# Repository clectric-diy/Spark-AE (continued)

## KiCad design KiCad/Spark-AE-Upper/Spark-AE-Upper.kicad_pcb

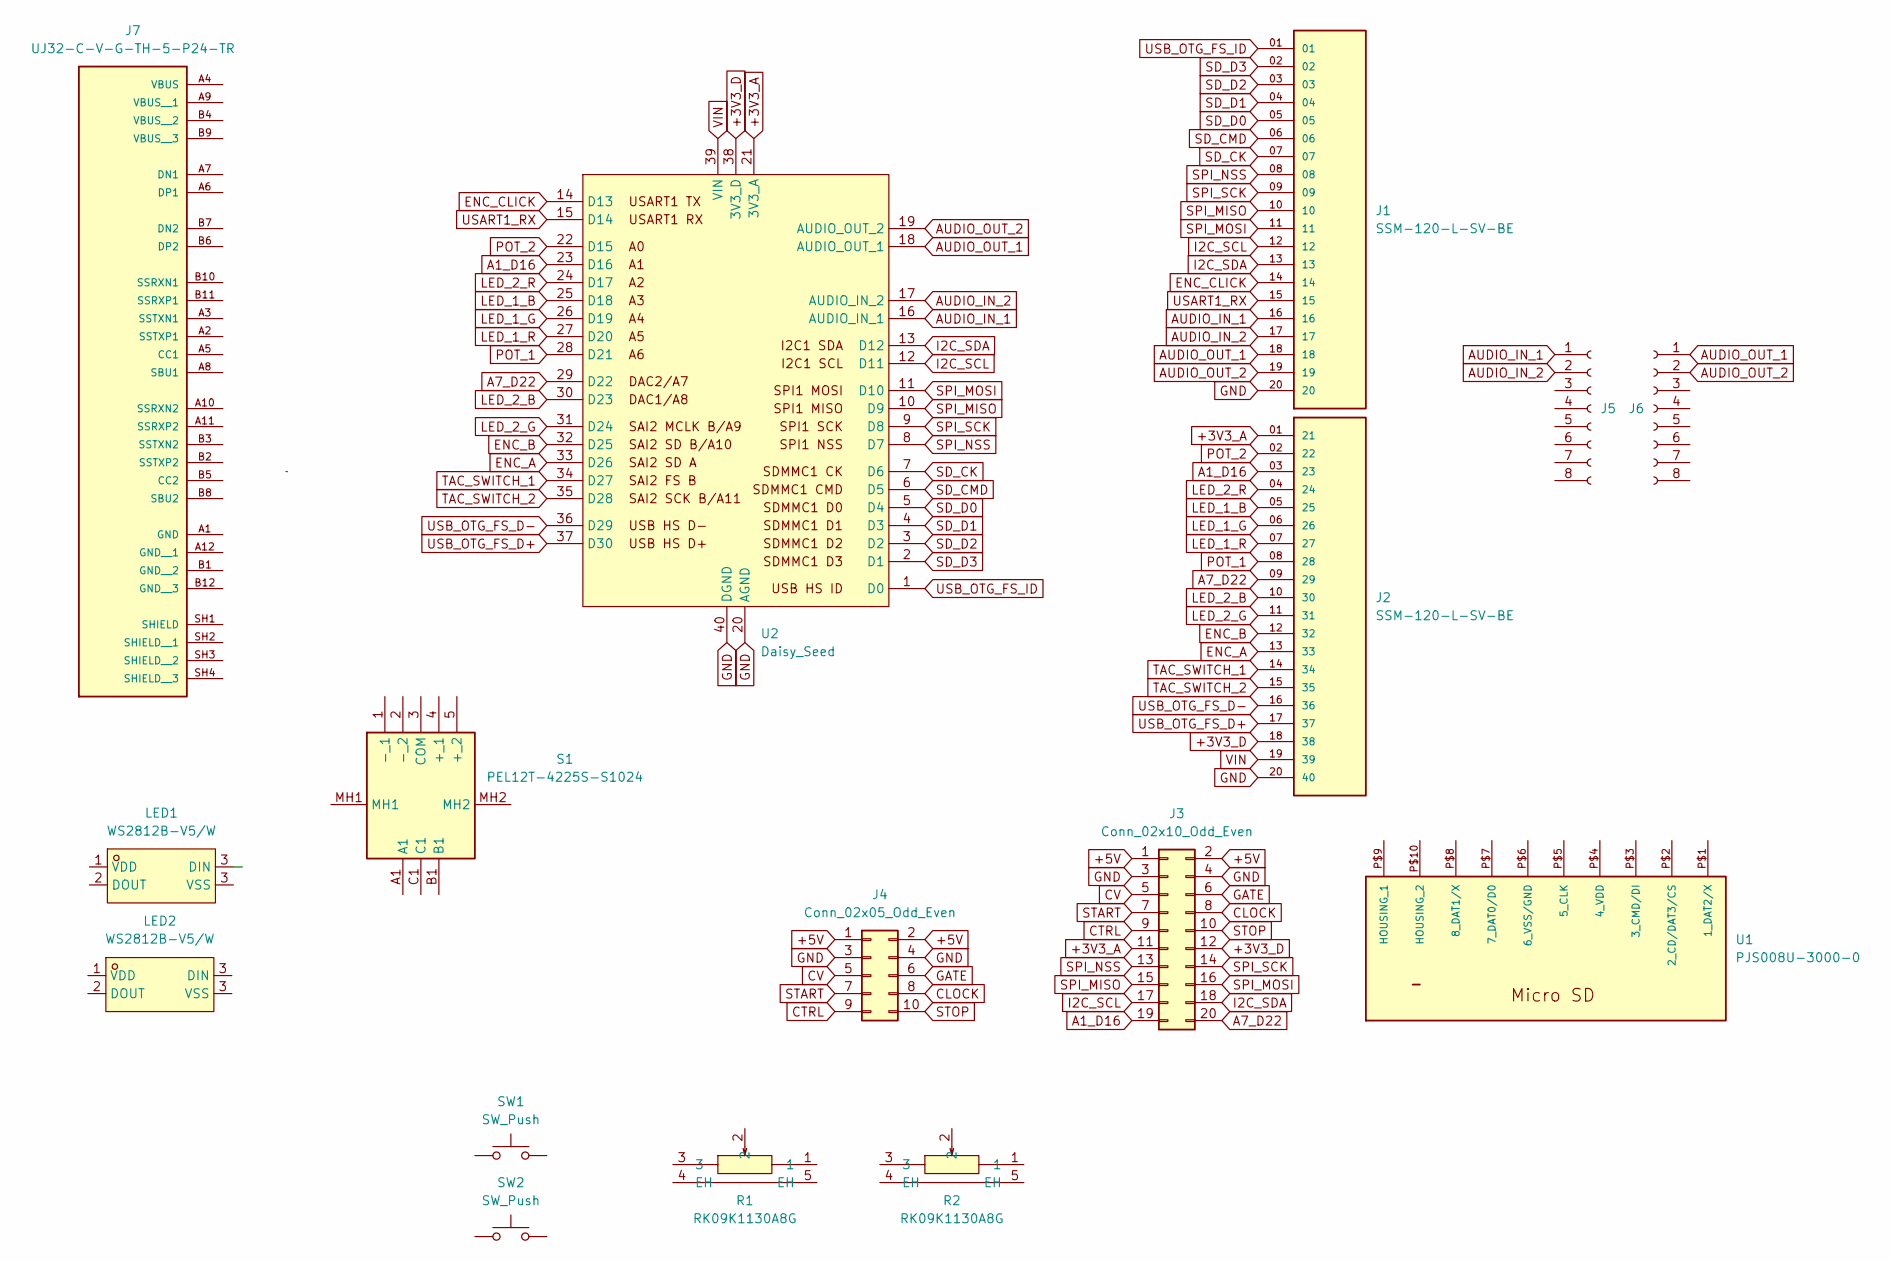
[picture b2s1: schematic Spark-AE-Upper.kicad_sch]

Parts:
J1, J2: SSM-120-L-SV-BE; SAMTEC_SSM-120-L-SV-BE
J3: Conn_02x10_Odd_Even; PinHeader_2x10_P2.54mm_Vertical
J4: Conn_02x05_Odd_Even; PinHeader_2x05_P2.54mm_Vertical
J5, J6: Conn_01x08_Socket; PinSocket_1x08_P2.54mm_Vertical
J7: UJ32-C-V-G-TH-5-P24-TR; SAMESKY_UJ32-C-V-G-TH-5-P24-TR; PARTREV 1.0
LED1, LED2: WS2812B-V5/W; LED-SMD_4P-L5.0-W5.0-TL-1; LCSC Part C2874885
R1, R2: RK09K1130A8G; RES-TH_RK09K113004U; LCSC Part C470294
S1: PEL12T-4225S-S1024; PEL12T4225SS1024; Mouser Part Number 652-PEL12T4225SS1024
SW1, SW2: SW_Push; SW_PUSH_6mm
U1: PJS008U-3000-0
U2: Daisy_Seed; DAISY_SEED

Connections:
+3V3_A: J2.01 (21), J3.11, U2.21 (3V3_A)
+3V3_D: J2.18 (38), J3.12, U2.38 (3V3_D)
+5V: J3.1, J3.2, J4.1, J4.2
A1_D16: J2.03 (23), J3.19, U2.23 (D16)
A7_D22: J2.09 (29), J3.20, U2.29 (D22)
AUDIO_IN_1: J1.16, J5.1, U2.16 (AUDIO_IN_1)
AUDIO_IN_2: J1.17, J5.2, U2.17 (AUDIO_IN_2)
AUDIO_OUT_1: J1.18, J6.1, U2.18 (AUDIO_OUT_1)
AUDIO_OUT_2: J1.19, J6.2, U2.19 (AUDIO_OUT_2)
CLOCK: J3.8, J4.8
CTRL: J3.9, J4.9
CV: J3.5, J4.5
ENC_A: J2.13 (33), U2.33 (D26)
ENC_B: J2.12 (32), U2.32 (D25)
ENC_CLICK: J1.14, U2.14 (D13)
GATE: J3.6, J4.6
GND: J1.20, J2.20 (40), J3.3, J3.4, J4.3, J4.4, U2.20 (AGND), U2.40 (DGND)
I2C_SCL: J1.12, J3.17, U2.12 (D11)
I2C_SDA: J1.13, J3.18, U2.13 (D12)
LED_1_B: J2.05 (25), U2.25 (D18)
LED_1_G: J2.06 (26), U2.26 (D19)
LED_1_R: J2.07 (27), U2.27 (D20)
LED_2_B: J2.10 (30), U2.30 (D23)
LED_2_G: J2.11 (31), U2.31 (D24)
LED_2_R: J2.04 (24), U2.24 (D17)
POT_1: J2.08 (28), U2.28 (D21)
POT_2: J2.02 (22), U2.22 (D15)
SD_CK: J1.07, U2.7 (D6)
SD_CMD: J1.06, U2.6 (D5)
SD_D0: J1.05, U2.5 (D4)
SD_D1: J1.04, U2.4 (D3)
SD_D2: J1.03, U2.3 (D2)
SD_D3: J1.02, U2.2 (D1)
SPI_MISO: J1.10, J3.15, U2.10 (D9)
SPI_MOSI: J1.11, J3.16, U2.11 (D10)
SPI_NSS: J1.08, J3.13, U2.8 (D7)
SPI_SCK: J1.09, J3.14, U2.9 (D8)
START: J3.7, J4.7
STOP: J3.10, J4.10
TAC_SWITCH_1: J2.14 (34), U2.34 (D27)
TAC_SWITCH_2: J2.15 (35), U2.35 (D28)
USART1_RX: J1.15, U2.15 (D14)
USB_OTG_FS_D+: J2.17 (37), U2.37 (D30)
USB_OTG_FS_D-: J2.16 (36), U2.36 (D29)
USB_OTG_FS_ID: J1.01, U2.1 (D0)
VIN: J2.19 (39), U2.39 (VIN)

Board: 2 copper layers, 16 parts (3 on the bottom side), 46 nets, no tracks yet.

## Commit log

2025-07-31 Create LICENSE
2025-08-03 Rebranding
    I'm rebranding everything to respect Electrosmith's trademarks. I got carried away. The new names align with the company name and make more sense anyway.
2025-08-08 Explaining the CERN OHL implications.
2025-08-09 I bumped my head and the ~~flux capacitor~~ Arc was revealed.
2025-08-09 Adding stubs for Arc modules.
2025-08-09 Removing the clectric Branding from the Arc modules.
2025-08-09 Initial commit of KiCad files
2025-08-09 Ignoring KiCad cache and backups
2025-08-09 Added Daisy Seed
2025-08-10 Create CONTRIBUTING.md file with contribution guidelines.
2025-08-10 Update README.md
    Added reference and link to the Daisy Seed in the Features section.
2025-08-15 Updating Contrib
2025-08-16 Adding docs directory.
2025-08-18 Moving _config.yml
2025-08-18 Oops, wrong theme.
2025-08-19 Added Electrosmith Source Docs
2025-08-22 Adding 1st Sketches of Spark-AE
2025-08-22 Added 1st Sketch and Updated Design Goals
2025-08-22 bump for pages
2025-08-22 Remove Download visit GitHub
2025-08-22 Font looked weird.
2025-08-22 panels not faceplates
2025-08-22 Moving KiCad files into subdirectory
2025-08-24 Cleaning up extra file in repo and README headings
2025-08-24 Apparently Markdown Syntax not supported.
2025-08-24 Standard FUNDING & gitignore
2025-09-01 Adding pdf version of module dimensions for Quickswap Case
2025-09-01 Committed to wrong repo.
2025-09-02 Reducing Headers and Updating Protoboards link.
2025-09-03 Ignoring Gerbers. Trust but verify.
2025-10-12 Found an Rotary Encoder that I think will match the AE style.
2025-10-13 Removing because part is not tested and confirmed yet.
2025-10-13 Roughing out the basic edges and control layout.
2026-01-14 removed led holes in favor of transparent pots
2026-01-14 renamed initial to panel and added other pcb projects
2026-01-14 filled in title blocks
2026-01-15 bumping copyright year
2026-01-15 updated to use components from clectric-diy's library
2026-01-22 laid out upper board interface and connections
2026-01-22 added first render of the pcb
2026-01-23 added and connected nets for daisy seed socket
2026-01-23 updated footprints and models
2026-01-23 added nets for bus connectors
2026-01-23 repositioned daisy seed, usb c, and micro sd
2026-01-23 ignoring working files
2026-01-23 added nets for ae modular i/o headers
2026-01-24 renamed nets to match pod and added arc connector
2026-01-24 positioned arc connector and repositioned daisy seed
2026-01-24 repositioned switches
2026-02-01 removing lower pcb and renaming to reflect change
2026-02-01 reorganizing the location of the Arc files
2026-02-03 renamed board to reduce board count
2026-03-09 moving over progress from "Shock" (see desc)
    I attempted to create this Daisy Pod clone as an AE-1U module called the "Shock". As expected I couldn't make it work.
    I've moved my progress on the "Shock" schematic over to and replacing the work on the "Spark".
    I plan to go back to make the "Shock" a stripped down version of the "Spark" in an AE-1U format.
2026-03-10 initial committ of completely reworked schematic. thanks gemini!
2026-03-12 assigned footprints & sorted ratsnest
2026-03-21 adding kicad_dru file with constraints for JLCPCB manufacturing and assembly
2026-03-21 ignoring KiCad backup files
2026-03-21 schematic 100% complete. pcb layout around 50% complete.
2026-03-22 continuing to plug away at pcb layout
2026-03-23 I accdently upgraded to KiCad 10 via a `brew upgrade`. I committing before launching it just in case.
2026-03-27 pcb layout complete. ready for final pre-fab confirmation.
2026-03-27 ignoring kicad fabrication files.
2026-03-27 Revise README for Mk0 Prototype details and edits
    Updated README to reflect changes in the Mk0 Prototype and removed a line about vertical symmetry.
2026-03-27 mk0 prototype sent for production! commit includes a couple of necessary tweaks.
2026-03-27 mk0 render for project readme
2026-03-27 ignoring fabrication files
2026-04-11 Restructuring directories to separate Arcs and to allow for duplicate panels
2026-04-16 bumped version to Mk0.1 and corrected polarity of D4 on schematic
2026-04-26 renaming images to show mark progression
2026-04-26 adding Mk0.1 schematic
2026-04-26 testing serving GitHub Pages from docs
2026-04-26 renaming images for more accurate versioning
2026-04-26 renamed Mk0.0 prototype images
    Updated the image reference for the Mk0 Prototype render.
2026-04-26 updated to Mk0.0 for more accurate prototype versioning
2026-04-26 committing to GitHub Pages served from docs
2026-04-26 actually pulling GitHub Pages content over this time
2026-04-26 correctiing typo
2026-04-26 Fix image path for Mk0 Prototype in README
    Updated image path for Mk0 Prototype render in README.
2026-04-26 bumping version number
2026-04-26 reorganizing to allow for alternate panels
2026-04-26 moving arcs back under spark instead
2026-04-26 rough pass over original mk0.1 panel. needs confirmation.
2026-04-26 made lightburn version for fast prototyping
2026-04-29 removed front flash port. sorry.
